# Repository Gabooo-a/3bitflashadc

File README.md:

# 3bitflashadc
Create a schematic design of a 3-bit flash ADC and fabricate

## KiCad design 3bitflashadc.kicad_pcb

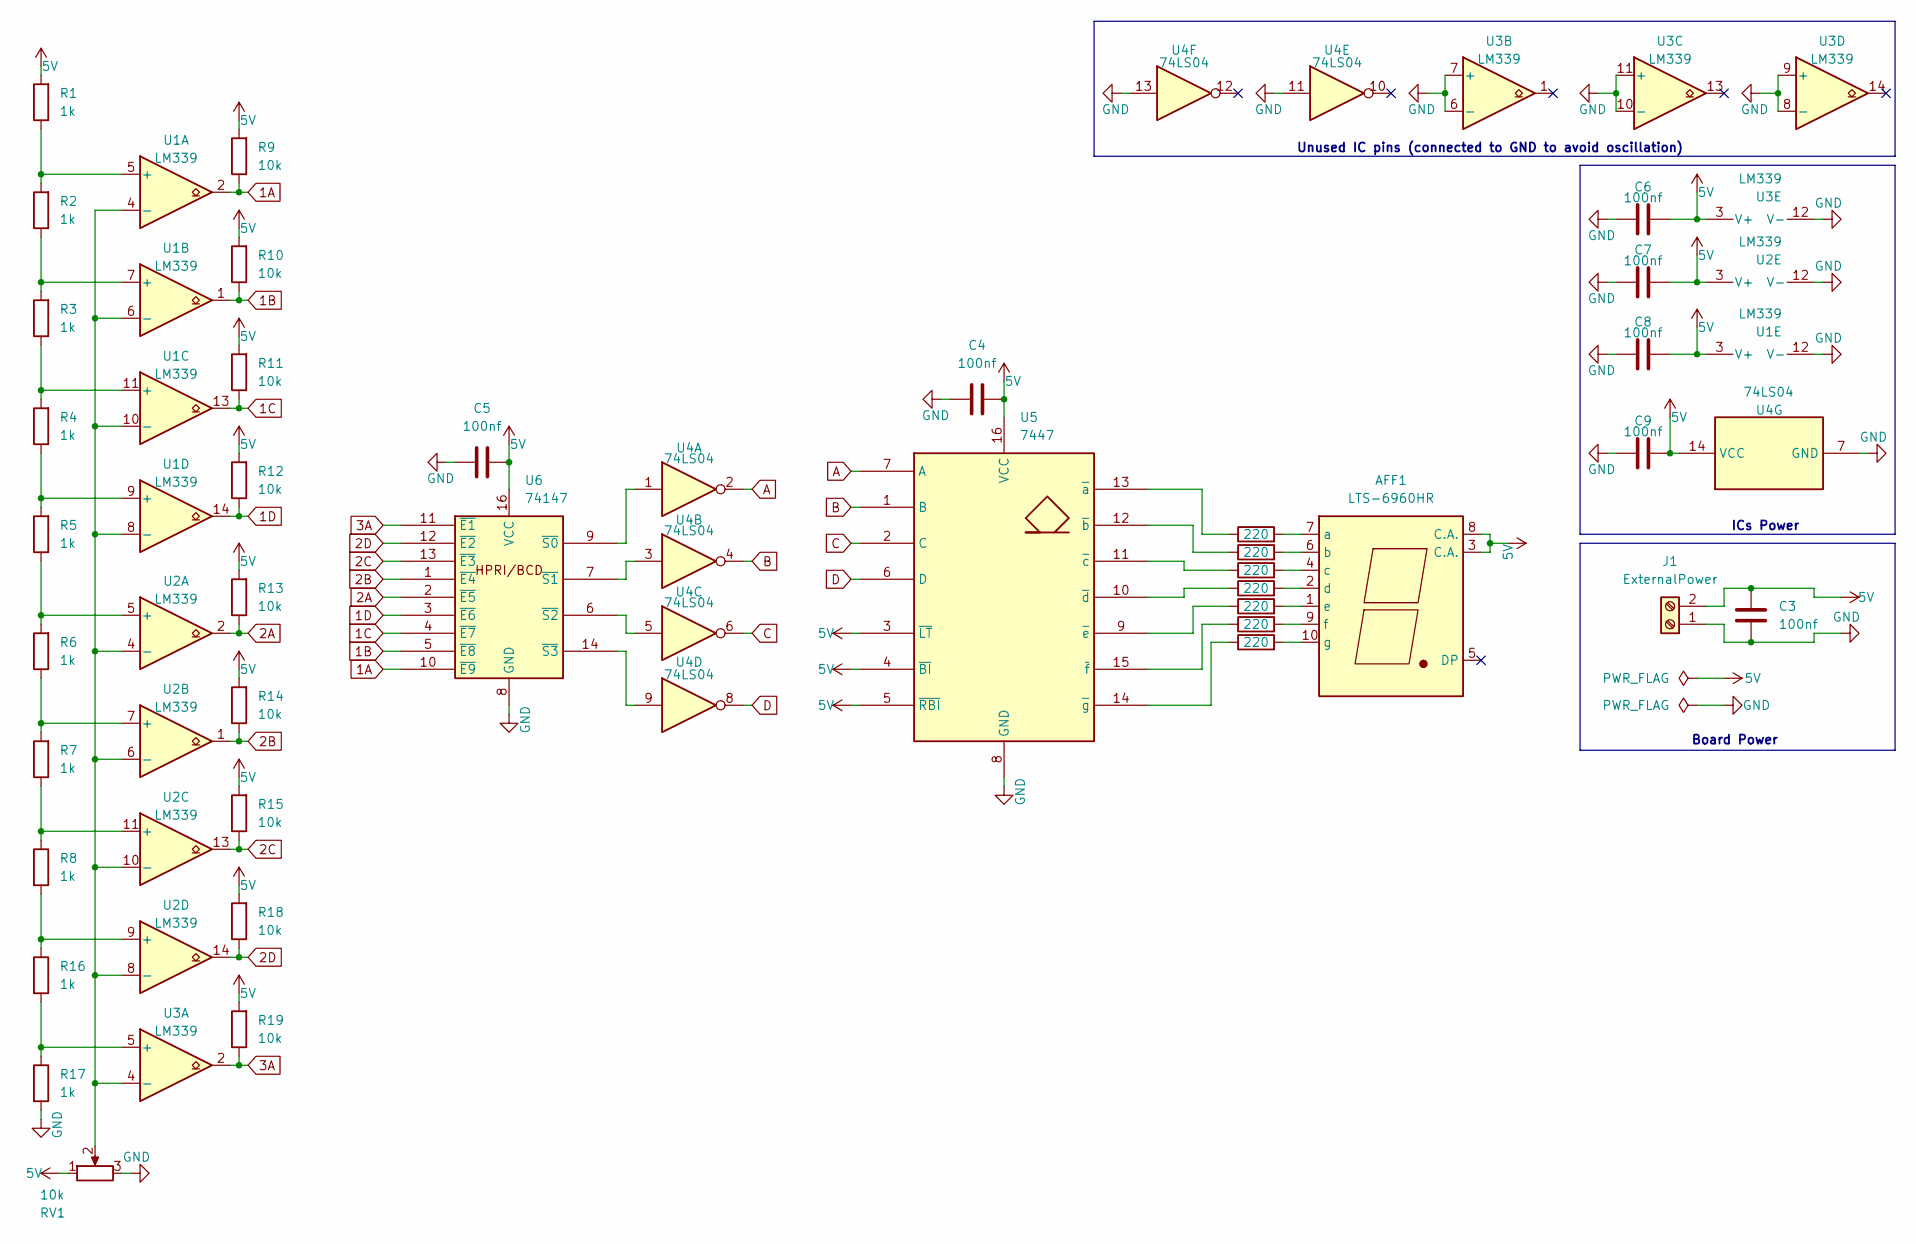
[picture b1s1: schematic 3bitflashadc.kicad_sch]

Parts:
AFF1: LTS-6960HR; 7SegmentLED_LTS6760_LTS6780
C3, C4, C5, C6, C7, C8, C9: 100nf; C_Disc_D3.4mm_W2.1mm_P2.50mm
J1: ExternalPower; TerminalBlock_MaiXu_MX126-5.0-02P_1x02_P5.00mm
R1, R2, R3, R4, R5, R6, R7, R8, R16, R17: 1k; R_Axial_DIN0207_L6.3mm_D2.5mm_P7.62mm_Horizontal
R9, R10, R11, R12, R13, R14, R15, R18, R19: 10k; R_Axial_DIN0207_L6.3mm_D2.5mm_P7.62mm_Horizontal
RV1: 10k; Potentiometer_Alpha_RD901F-40-00D_Single_Vertical
Ra1: 220; R_Axial_DIN0207_L6.3mm_D2.5mm_P7.62mm_Horizontal
Rb1: 220; R_Axial_DIN0207_L6.3mm_D2.5mm_P7.62mm_Horizontal
Rc1: 220; R_Axial_DIN0207_L6.3mm_D2.5mm_P7.62mm_Horizontal
Rd1: 220; R_Axial_DIN0207_L6.3mm_D2.5mm_P7.62mm_Horizontal
Re1: 220; R_Axial_DIN0207_L6.3mm_D2.5mm_P7.62mm_Horizontal
Rf1: 220; R_Axial_DIN0207_L6.3mm_D2.5mm_P7.62mm_Horizontal
Rg1: 220; R_Axial_DIN0207_L6.3mm_D2.5mm_P7.62mm_Horizontal
U1, U2, U3: LM339; CERDIP-14_W7.62mm_SideBrazed_LongPads_Socket
U4: 74LS04; CERDIP-14_W7.62mm_SideBrazed_LongPads_Socket
U5: 7447; CERDIP-16_W7.62mm_SideBrazed_Socket
U6: 74147; CERDIP-16_W7.62mm_SideBrazed_Socket

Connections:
1A: R9.1, U1.2, U6.10 (~E9)
1B: R10.1, U1.1, U6.5 (~E8)
1C: R11.1, U1.13, U6.4 (~E7)
1D: R12.1, U1.14, U6.3 (~E6)
2A: R13.1, U2.2, U6.2 (~E5)
2B: R14.1, U2.1, U6.1 (~E4)
2C: R15.1, U2.13, U6.13 (~E3)
2D: R18.1, U2.14, U6.12 (~E2)
3A: R19.1, U3.2, U6.11 (~E1)
5V: AFF1.3 (C.A.), AFF1.8 (C.A.), C3.2, C4.2, C5.2, C6.2, C7.2, C8.2, C9.2, J1.2, R1.2, R9.2, R10.2, R11.2, R12.2, R13.2, R14.2, R15.2, R18.2, R19.2, RV1.1, U1.3 (V+), U2.3 (V+), U3.3 (V+), U4.14 (VCC), U5.3 (~LT), U5.4 (~BI), U5.5 (~RBI), U5.16 (VCC), U6.16 (VCC)
A: U4.2, U5.7 (A)
B: U4.4, U5.1 (B)
C: U4.6, U5.2 (C)
D: U4.8, U5.6 (D)
GND: C3.1, C4.1, C5.1, C6.1, C7.1, C8.1, C9.1, J1.1, R17.2, RV1.3, U1.12 (V-), U2.12 (V-), U3.6 (-), U3.7 (+), U3.8 (-), U3.9 (+), U3.10 (-), U3.11 (+), U3.12 (V-), U4.7 (GND), U4.11, U4.13, U5.8 (GND), U6.8 (GND)
unnamed: AFF1.7 (a), Ra1.2
unnamed: AFF1.6 (b), Rb1.2
unnamed: AFF1.4 (c), Rc1.2
unnamed: AFF1.2 (d), Rd1.2
unnamed: AFF1.1 (e), Re1.2
unnamed: AFF1.9 (f), Rf1.2
unnamed: AFF1.10 (g), Rg1.2
unnamed: R1.1, R2.2, U1.5 (+)
unnamed: RV1.2, U1.4 (-), U1.6 (-), U1.8 (-), U1.10 (-), U2.4 (-), U2.6 (-), U2.8 (-), U2.10 (-), U3.4 (-)
unnamed: R2.1, R3.2, U1.7 (+)
unnamed: R3.1, R4.2, U1.11 (+)
unnamed: R4.1, R5.2, U1.9 (+)
unnamed: R5.1, R6.2, U2.5 (+)
unnamed: R6.1, R7.2, U2.7 (+)
unnamed: R7.1, R8.1, U2.11 (+)
unnamed: R8.2, R16.1, U2.9 (+)
unnamed: R16.2, R17.1, U3.5 (+)
unnamed: Ra1.1, U5.13 (~a)
unnamed: Rb1.1, U5.12 (~b)
unnamed: Rc1.1, U5.11 (~c)
unnamed: Rd1.1, U5.10 (~d)
unnamed: Re1.1, U5.9 (~e)
unnamed: Rf1.1, U5.15 (~f)
unnamed: Rg1.1, U5.14 (~g)
unnamed: U4.1, U6.9 (~S0)
unnamed: U4.3, U6.7 (~S1)
unnamed: U4.5, U6.6 (~S2)
unnamed: U4.9, U6.14 (~S3)

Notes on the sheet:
Unused IC pins (connected to GND to avoid oscillation)
ICs Power
Board Power

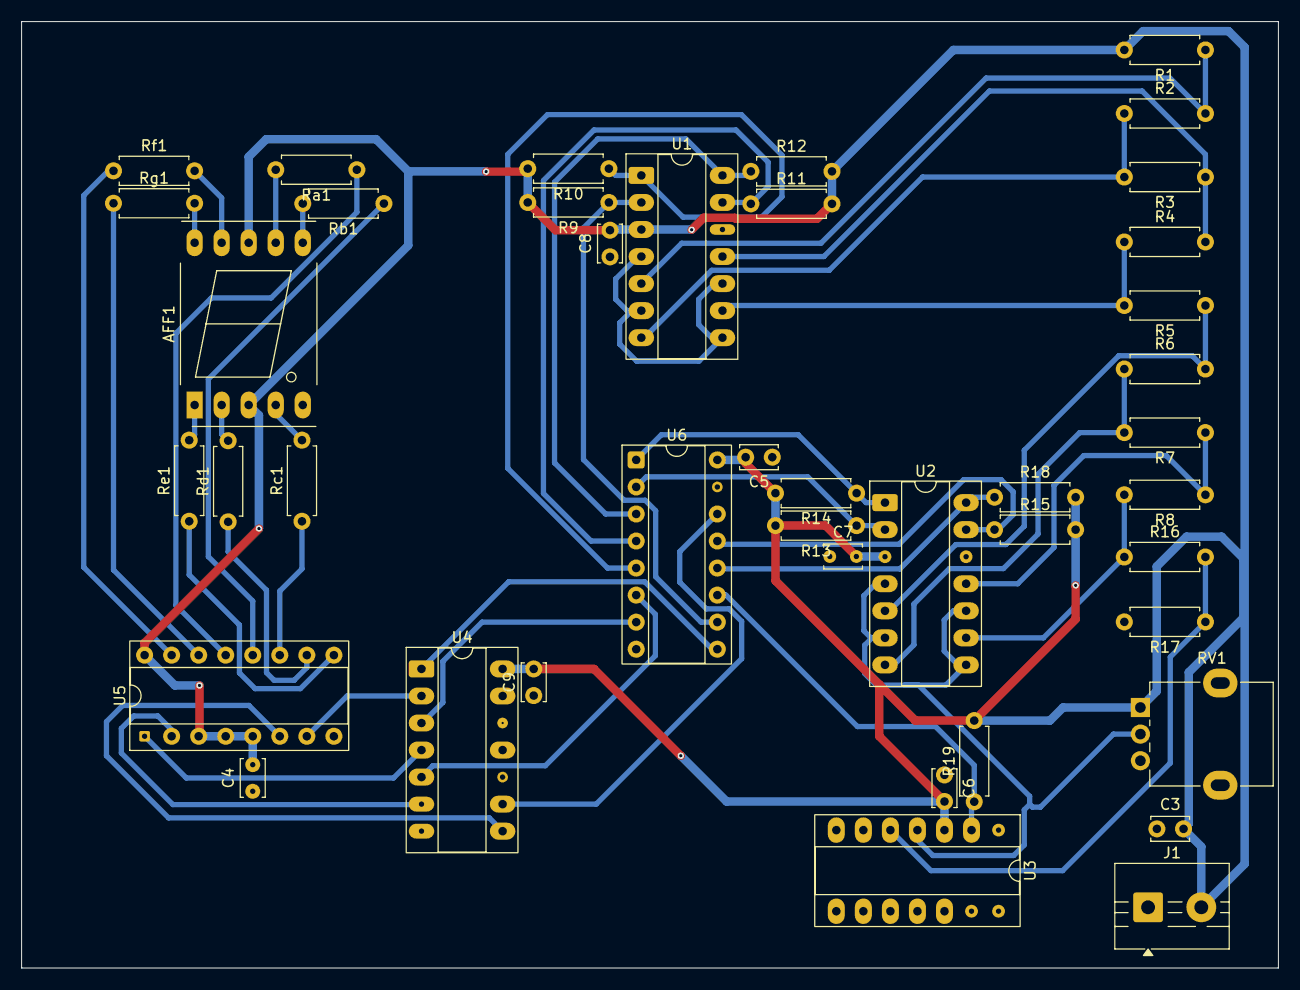
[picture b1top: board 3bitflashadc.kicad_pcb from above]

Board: 2 copper layers, 118.1 x 88.9 mm, 42 parts (0 on the bottom side), 43 nets.
